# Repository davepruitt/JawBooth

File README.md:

# JawBooth

This project is designed to assess cortical motor map changes due to pellet eating behavior paired with vagus nerve stimulation. In this project, we designed a booth in which rats are dispensed reward pellets at regular intervals. After a reward pellet is dispensed, we detect when the rat retrieves the reward pellet using an IR sensor that is positioned around the pellet receiver. Following retrieval of the pellet, we deliver vagus nerve stimulation to the rats. Our hypothesis is that vagus nerve stimulation will result in cortical map changes within motor cortex.

We primarily reused booths designed and built for previous studies. We did, however, design new doors for the booths that had a central pellet receiver / nosepoke with an attached IR sensor. We also designed a circuit board to mount directly onto this door. All designs for the new door, pellet receiver, and printed circuit board are located in the "CAD Designs" folder. The printed circuit board was initially designed in Eagle by Drew Sloan (Vulintus, Inc). I made further modifications with the assistance of Holle Carey (Vulintus, Inc) and Simran Singh (TxBDC). We printed the circuit board using a desktop PCB milling machine (https://www.bantamtools.com/products/bantam-tools-desktop-pcb-milling-machine). 

We designed the circuit board such that an Arduino Uno fits onto it. The purpose of the Arduino is to read the IR sensor data and transmit that data back to the computer, as well as send trigger signals to the pellet dispenser and to the neural stimulator. I wrote the code that resides on the Arduino board. It is written in C. The desktop code is written in C# and WPF. It manages a full session and presents a graphical user interface to the desktop user. It determines when feeds and stimulations will occur, and analyzes the IR signal data that it receives from the Arduino board.

Any questions can be directed to myself (David Pruitt). Feel free to contact me.

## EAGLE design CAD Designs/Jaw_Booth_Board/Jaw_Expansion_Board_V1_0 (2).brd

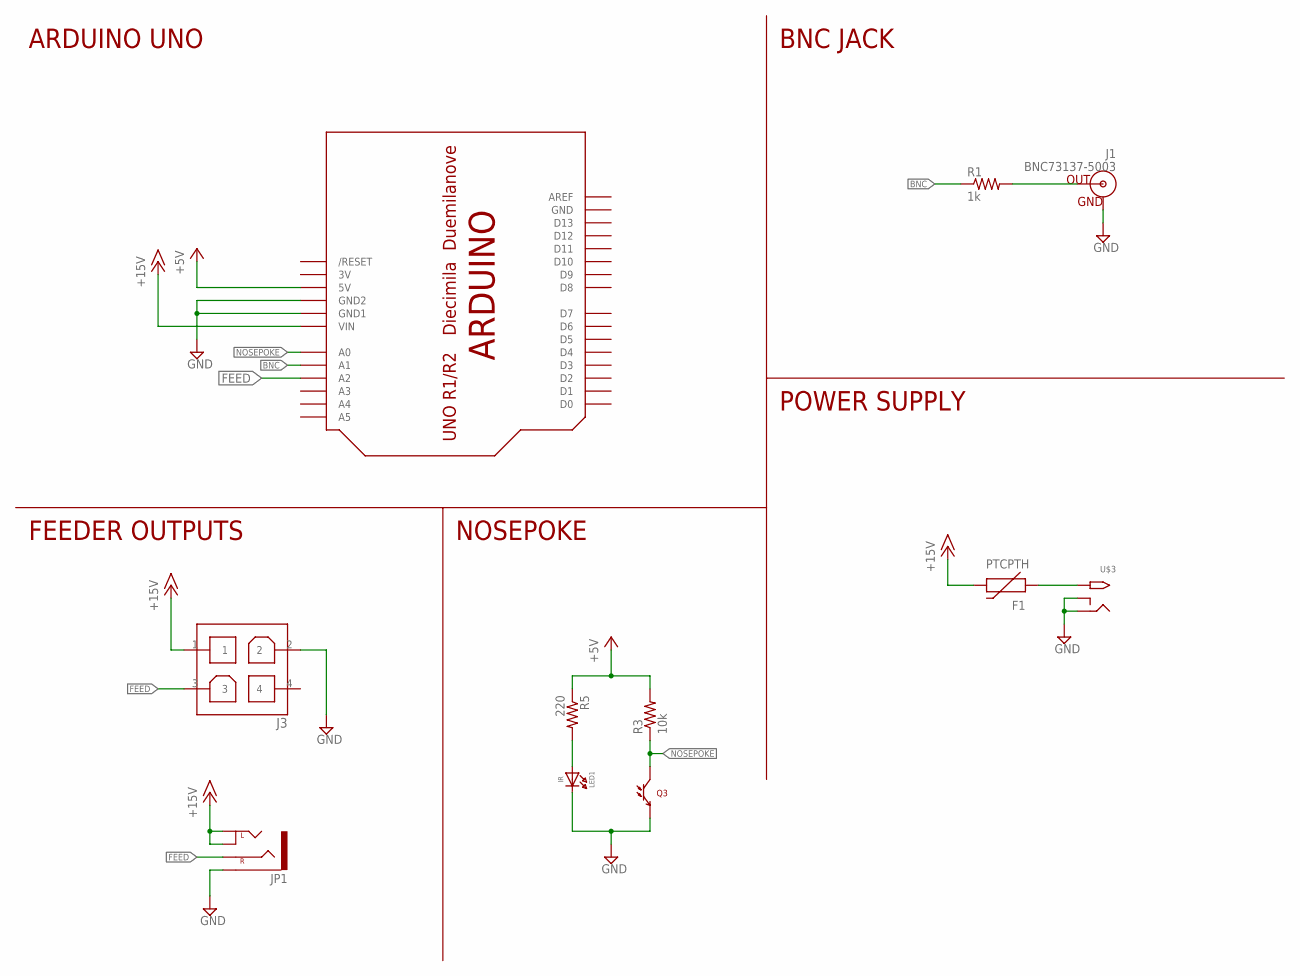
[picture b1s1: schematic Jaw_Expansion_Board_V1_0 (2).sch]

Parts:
F1: PTCPTH; PTC
J1: BNC73137-5003; BNC_73137-5003
J3: MOLEX_MINI-FIT_MALE_HEADER_2X2MOLEX_87427_MINI-FI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; MOLEX_87427_MINI-FIT_2X2_RA
JP1: 3.5MM_STEREORA; 161-3509-E
LED1: IR; LTR-301
Q3: LTR-301
R1: 1k; AXIAL-0.4
R3: 10k; AXIAL-0.4
R5: 220; AXIAL-0.4
U$1: ARDUINO_UNOUNO_NO_HOLES; ARDUINO-NOHOLE
U$3: 2.1MMJACKTHM; PJ-102A

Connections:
3V: U$1.3V
+5V: R3.P$2 (2), R5.P$1 (1), U$1.5V
+15V: F1.P$2 (2), J3.1, JP1.L (LEFT1), JP1.L2 (LEFT2), U$1.VIN
BNC: R1.P$1 (1), U$1.A1
FEED: J3.3, JP1.R (RIGHT), U$1.A2
GND: J1.GND, J3.2, JP1.SHD, LED1.- (C), Q3.- (E), U$1.GND, U$1.GND1, U$1.GND2, U$3.RING, U$3.RING_SW
unnamed: J1.S (OUT), R1.P$2 (2)
unnamed: F1.P$1 (1), U$3.TIP
unnamed: LED1.+ (A), R5.P$2 (2)
NOSEPOKE: Q3.+ (C), R3.P$1 (1), U$1.A0

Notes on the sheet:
ARDUINO UNO
BNC JACK
POWER SUPPLY
NOSEPOKE
FEEDER OUTPUTS

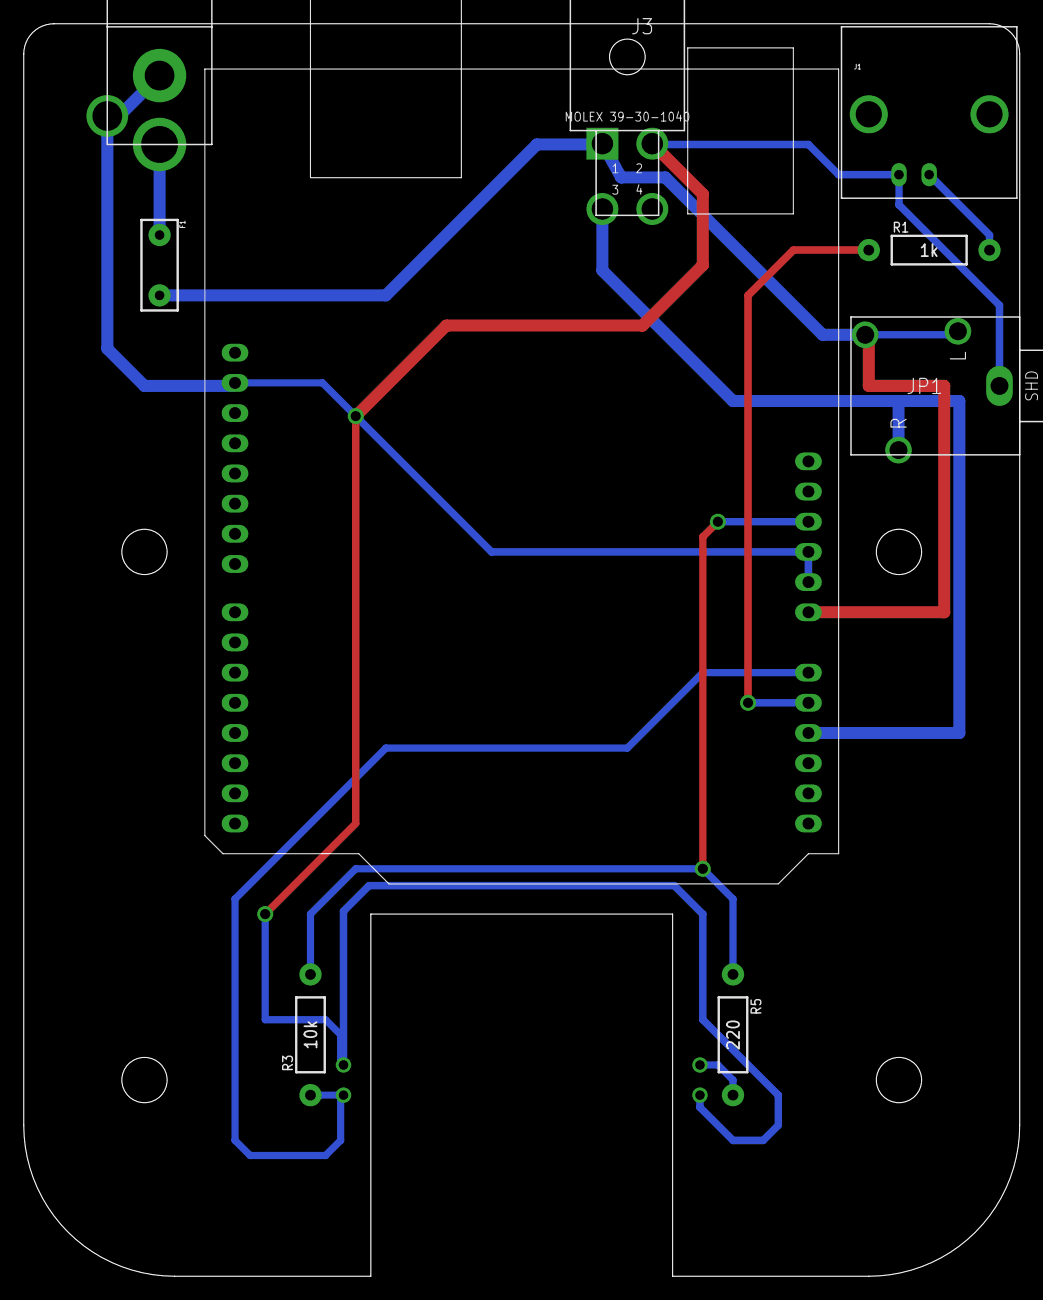
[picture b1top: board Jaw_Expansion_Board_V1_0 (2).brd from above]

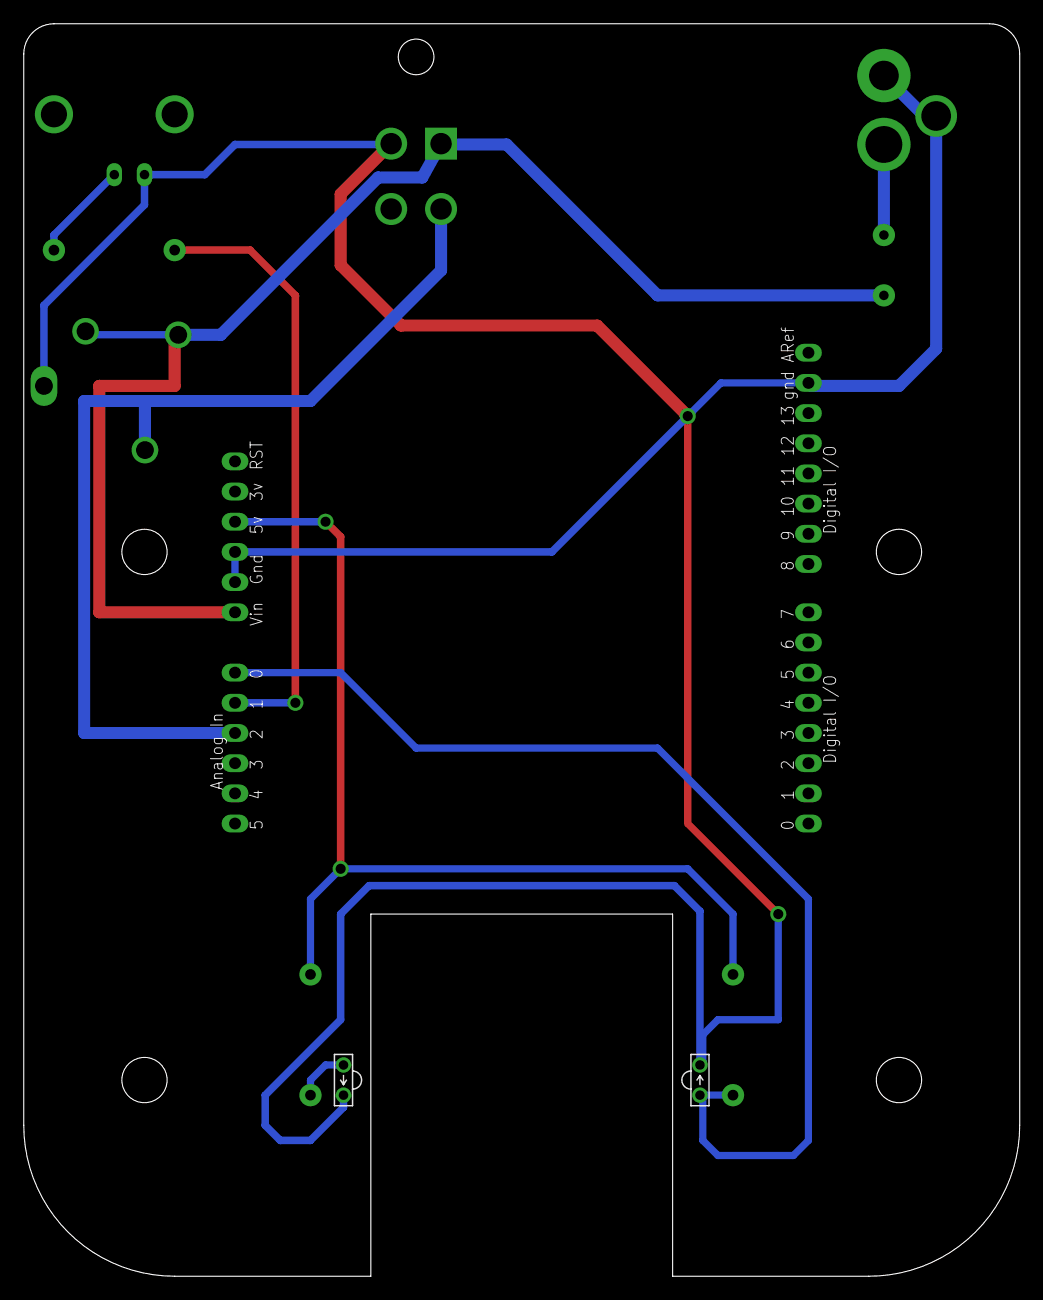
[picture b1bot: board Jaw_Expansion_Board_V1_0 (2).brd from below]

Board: 2 copper layers, 83.8 x 105.4 mm, 11 parts (3 on the bottom side), 9 nets.

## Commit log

2018-03-05 Initial commit
    Initial commit

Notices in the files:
parts and their libraries:
SparkFun-PowerIC: Licensing: Creative Commons ShareAlike 4.0 International - https://creativecommons.org/licenses/by-sa/4.0
